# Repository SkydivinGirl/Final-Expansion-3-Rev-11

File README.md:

# Final-Expansion-3-Rev-11
VIC-20 Final Expansion 3 Rev 11 Cartridge

This repository contains everything needed to produce a Final Expansion Rev 11 cartridge for the VIC-20 computer.  It's a bit unorganized but the latest versions of the files should be the ones to use.

This project was created to make assembly easier than earlier versions of the Final Expansion 3 cartridge.

The board layouts were created by Fredric Blåholtz.  The 3D case design were created by Thomas Christoph.  The labels, BOM, and most of the other project files were created by Heather Kent.  Preloaded games were prvided by Jeff Daniels of the VIC-20 Denial forum (sleepingelephant.com/ipw-web/bulletin/bb/index.php).  Firmware and other files were created by others.

The 3D Case design has a different license that allows for printing your own case but you are not allowed to sell them.  Read the license in the zip file for details on the license limitations.

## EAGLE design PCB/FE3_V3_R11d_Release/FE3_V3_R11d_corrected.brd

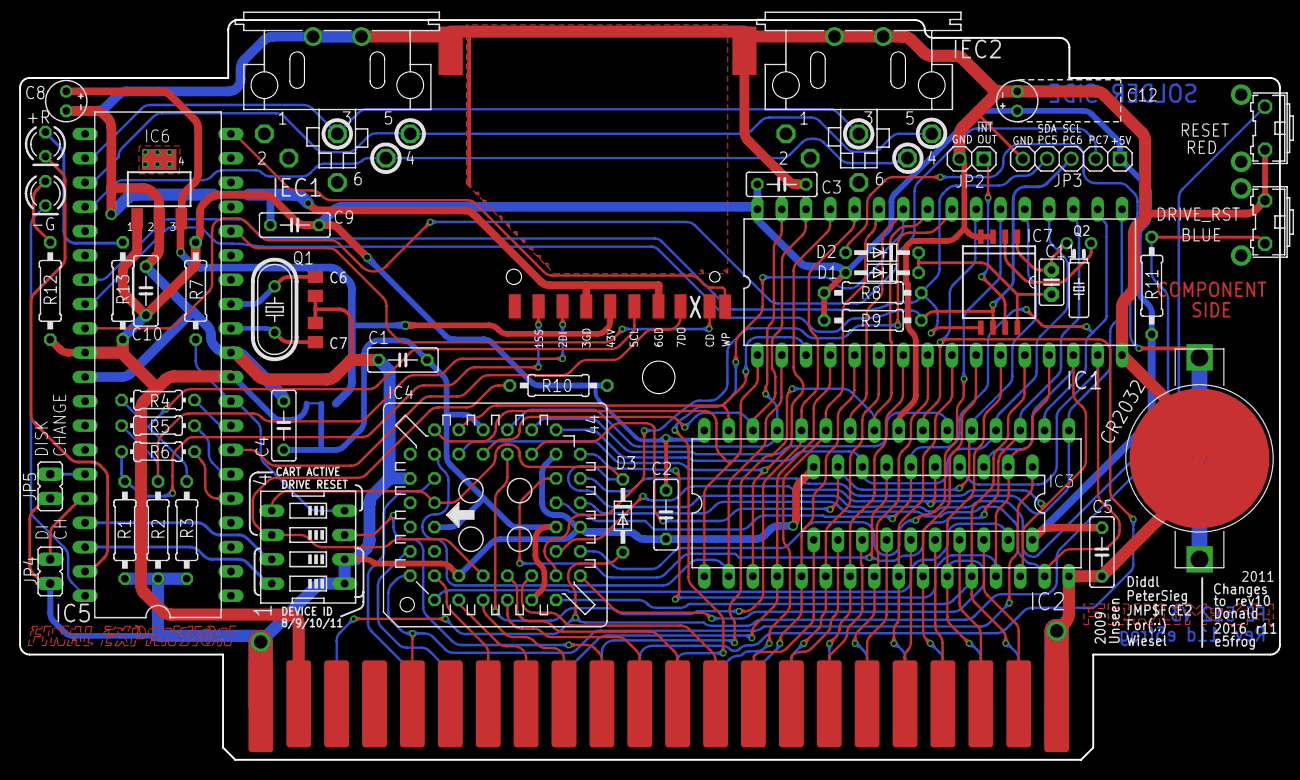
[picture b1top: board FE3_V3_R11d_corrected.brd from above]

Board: 2 copper layers, 131.7 x 77.3 mm, 63 parts (1 on the bottom side), 88 nets.

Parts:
1SS, 2DI, 3GD, 5CL, 6GD, 7DO, 43V: SMD1,27-2,54
+R: LED3MM
-G: LED3MM
C1, C2, C3, C4, C5, C9, C10: 100nF; C050-025X075
C6, C7: 33pF; C0805K
C8: 22µF; E2-4
C11: 22pF; C2.5-2
C12: 100µF; E2-4
CD: SMD1,27-2,54
CR2032: CR2032_RETAINER_PK5
D1, D2, D3: BAT85; DO34-7
DEVICE: EDG-04
DRIVE_RST: B3F-31XX
IC1: AM29F040B; DIL32
IC2: 4Mb-55; DIL32
IC3: 74LS245N; DIL20
IC4: CPLD-ATF1504-AS; S44
IC5: ATMEGA1284P; DIL40
IC6: 3V3REG_1703; SOT223
IC7: PCF8583T; SOT176-1
IEC1, IEC2: MAB6H
JP2: 1X02
JP3: 1X05
JP4, JP5: JP1
NC_9: SMD1,27-2,54
PAD1, PAD2: SMD2,54-5,08
Q1: 8.000MHz; HC49U-V
Q2: 32768Hz; TC26H
R1, R2, R3: 3k3; 0207/10
R4, R5, R6: 1k8; 0204/7
R7, R10, R11: 10k; 0207/10
R8, R9: 1k8; 0207/10
R12, R13: 470; 0207/10
RESET: B3F-31XX
U$2: VIC-20_EXPANSION
V-INT: SJ_2
WP: SMD1,27-2,54

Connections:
3V3: 43V.1, C8.+, IC6.3, V-INT.1
!C_RESET: D3.A, RESET.2, U$2.P$25
!RESET: D3.C, DEVICE.5, DRIVE_RST.1, IC4.1, R11.1
!WE: IC1.31, IC2.29, IC4.33
+5V: C2.1, C3.1, C5.1, C9.1, C10.1, C12.+, D1.A, IC1.32, IC2.32, IC3.20, IC5.10, IC5.30, IC6.1, JP3.1, R7.2, R8.2, R9.2, R10.1, R11.2, R12.1, R13.1, U$2.P$2, V-INT.3
A0: IC1.12, IC2.12, IC4.17, U$2.P$43
A1: IC1.11, IC2.11, IC4.18, U$2.P$42
A2: IC1.10, IC2.10, U$2.P$41
A3: IC1.9, IC2.9, U$2.P$40
A4: IC1.8, IC2.8, U$2.P$39
A5: IC1.7, IC2.7, U$2.P$38
A6: IC1.6, IC2.6, U$2.P$37
A7: IC1.5, IC2.5, U$2.P$36
A8: IC1.27, IC2.27, U$2.P$35
A9: IC1.26, IC2.26, U$2.P$34
A10: IC1.23, IC2.23, U$2.P$33
A11: IC1.25, IC2.25, U$2.P$32
A12: IC1.4, IC2.4, U$2.P$31
A13: IC1.28, IC2.28, IC4.34
A14: IC1.29, IC2.3, IC4.38
A15: IC1.3, IC2.31, IC4.37
A16: IC1.2, IC2.2, IC4.41
A17: IC1.30, IC2.30, IC4.36
A18: IC1.1, IC2.1, IC4.39
BLK1: IC4.16, U$2.P$13
BLK2: IC4.14, U$2.P$12
BLK3: IC4.13, U$2.P$11
BLK5: DEVICE.6, IC4.12, R10.2
CD0: IC3.18, U$2.P$21
CD1: IC3.17, U$2.P$20
CD2: IC3.16, U$2.P$19
CD3: IC3.15, U$2.P$18
CD4: IC3.14, U$2.P$17
CD5: IC3.13, U$2.P$16
CD6: IC3.12, U$2.P$15
CD7: IC3.11, U$2.P$14
C_BLK5: DEVICE.3, U$2.P$10
C_R/W: IC3.1, IC4.6, U$2.P$5
D0: IC1.13, IC2.13, IC3.2, IC4.28
D1: IC1.14, IC2.14, IC3.3, IC4.26
D2: IC1.15, IC2.15, IC3.4, IC4.24
D3: IC1.17, IC2.17, IC3.5, IC4.21
D4: IC1.18, IC2.18, IC3.6, IC4.25
D5: IC1.19, IC2.19, IC3.7, IC4.27
D6: IC1.20, IC2.20, IC3.8, IC4.29
D7: IC1.21, IC2.21, IC3.9, IC4.32
EE/CE: IC1.22, IC4.20
EE/OE: IC1.24, IC4.19
G: IC3.19, IC4.7
GND: 3GD.1, 6GD.1, C1.2, C2.2, C3.2, C4.2, C5.2, C6.2, C7.2, C8.-, C9.2, C10.2, C12.-, CR2032.P$3, DEVICE.1, DEVICE.2, DRIVE_RST.2, IC1.16, IC2.16, IC2.24, IC3.10, IC4.10, IC4.22, IC4.30, IC4.42, IC5.11, IC5.31, IC6.2, IC7.3, IC7.4, IEC1.PE, IEC1.PE@, IEC2.PE, IEC2.PE@, JP2.2, JP3.5, JP4.1, JP5.1, PAD1.1, PAD2.1, R1.1, R2.1, R3.1, RESET.1, U$2.P$1, U$2.P$22, U$2.P$23, U$2.P$44
I2C_N: IC5.27, IC7.5, JP3.4, R8.1
I2C_P: IC5.28, IC7.6, JP3.3, R9.1
IEC_ATN: IC5.22, IEC1.3, IEC2.3
IEC_CLK: IC5.24, IEC1.4, IEC2.4
IEC_DATA: IC5.23, IEC1.5, IEC2.5
IO3: IC4.4, U$2.P$28
LED_GREEN: -G.K, IC5.40
LED_RED: +R.K, IC5.39
unnamed: DEVICE.7, IC5.37
unnamed: IC5.36, JP4.2
unnamed: IC5.35, JP5.2
unnamed: +R.A, R13.2
unnamed: DEVICE.8, IC5.38
unnamed: IC5.29, JP3.2
unnamed: -G.A, R12.2
unnamed: IC5.8, R4.2
unnamed: IC5.6, R5.2
unnamed: IC5.5, R6.2
unnamed: DEVICE.4, IC5.9, R7.1
unnamed: CR2032.P$1, CR2032.P$2, D2.A
unnamed: C7.1, IC5.12, Q1.2
unnamed: C6.1, IC5.13, Q1.1
unnamed: C11.1, D1.C, D2.C, IC7.8
unnamed: C11.2, IC7.1, Q2.2
unnamed: IC7.2, Q2.1
unnamed: IC7.7, JP2.1
RAM1: IC4.11, U$2.P$9
RAM2: IC4.9, U$2.P$8
RAM3: IC4.8, U$2.P$7
RAM/CS: IC2.22, IC4.31
S02: IC4.43, U$2.P$27
SD_CARD_DETECT: CD.1, IC5.16
SD_CARD_SELECT: 1SS.1, R1.2, R6.1
SD_CLOCK: 5CL.1, R3.2, R4.1
SD_DATA_IN: 2DI.1, R2.2, R5.1
SD_DATA_OUT: 7DO.1, IC5.7
SD_WR_PROTECT: IC5.20, WP.1
VCCINT: C1.1, C4.1, IC4.3, IC4.15, IC4.23, IC4.35, V-INT.2

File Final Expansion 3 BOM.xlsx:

Qty | Loc | Markings | Description | Manufacturer # | DigiKey # | Mouser # | Notes
1 | SD | PD00305A | Memory Card Connectors SD CARD RT ANGLE SURF MT PUSH-PUSH | SD-RSMT-2-MQ | 3M5646CT-ND | 517-SD-RSMT-2-MQ
1 | IC6 | MCP1703 | LDO Voltage Regulators Low Iq 250mA LDO Vin 16V maxVout 3.3V | MCP1703-3302E/DB | MCP1703-3302E/DB-ND | 579-MCP1703-3302E/DB
2 | C6,C7 |  | Multilayer Ceramic Capacitors MLCC - SMD/SMT 0603 33pF 50volts C0G 1% | GRM1885C1H330FA01D | 490-9720-1-ND | 81-GRM39C330F50
1 | IC7 | 8583T | Real Time Clock CLK/CALENDAR 240X8 RAM | PCF8583T/5,518 | 568-1085-1-ND | 771-PCF8583TD-T
3 | R1,R2,R3 | O,O R,G | Carbon Film Resistors - Through Hole 3.3K ohm 1/4W 5% | CFR-25JR-52-3K3 | 3.3KQBK-ND | 603-CFR-25JR-523K3
5 | R4,R5,R6,R8,R9 | BR,GRY,R,G | Carbon Film Resistors - Through Hole 1.8K ohm 1/4W 5% | CFR-25JR-52-1K8 | 1.8KQBK-ND | 603-CFR-25JR-521K8
3 | R7,R10,R11 | BR,BL,O,G | Carbon Film Resistors - Through Hole 10K ohm 1/4W 5% | CFR-25JR-52-10K | 10KQBK-ND | 603-CFR-25JR-5210K
2 | R12,R13 | Y,P,BR,G | Carbon Film Resistors - Through Hole 470ohm 1/4W 5% | CFR-25JR-52-470R | 470QBK-ND | 603-CFR-25JR-52470R
3 | D1,D2,D3 |  | Schottky Diodes & Rectifiers SCHOTTKY 30V 200MA | BAT85,113 | 568-1617-1-ND | 771-BAT85-T/R
7 | C1,C2,C3,C4,C5,C9,C10 | 104J | Multilayer Ceramic Capacitors MLCC - Leaded 0.1uF 50volts C0G 5% Radial | FG26C0G1H104JNT06 | 445-173396-1-ND | 810-FG26C0G1H104JNT6
1 | C11 | 220 | Multilayer Ceramic Capacitors MLCC - Leaded 22pF 50volts C0G 5% Radial | FG18C0G1H220JNT06 | 445-173182-1-ND | 810-FG18C0G1H220JNT6
1 | C8 | 22uF10V | Aluminum Electrolytic Capacitors - Leaded 10volts 22uF 4x7 20% 1.5LS | UPW1A220MDD6 | 493-1728-ND | 647-UPW1A220MDD6
1 | C12 | 100uF10V | Aluminum Electrolytic Capacitors - Leaded 100uF 10 Volts 20% | UPW1A101MDD1TD | 493-11391-1-ND | 647-UPW1A101MDD1TD
11 | JP2,JP3,JP4,JP5 |  | 11 Positions Header, Unshrouded Connector 0.100" (2.54mm) Through Hole Gold | 61301411121 | 732-5325-ND | 710-61301411121 | 40-PIN Alternative 61304011121
1 | Q1 | A080F6F | Crystals +/-20ppm 8MHZ FUNDAMENTAL | ABL-8.000MHZ-B2 | 535-9062-ND | 815-ABL-8-B2
1 | Q2 | 32.768000000000001 | Crystals 32.768KHz | AB26T-32.768KHZ | 535-9032-ND | 815-AB26T-32.768KHZ
1 | LED+R |  | Standard LEDs - Through Hole WL-TMRC THT Mono Diffusd Rnd3mm SprRd | 151031SS06000 | 732-5006-ND | 710-151031SS06000 | Alternative? SLX-LX3054ID
1 | LED-G |  | Standard LEDs - Through Hole WL-TMRC THT Mono Diffusd Rnd3mm BrtGn | 151031VS06000 | 732-5008-ND | 710-151031VS06000
2 | IEC |  | Circular DIN Connectors DIN, 6P jack, rt, through hole | SDS-60J | CP-2360-ND | 490-SDS-60J
1 | SW1 | CTS 206-4 | DIP Switches / SIP Switches SPST 4 switch sections | 206-4 | CT2064-ND | 774-2064
1 | B1 |  | Tactile Switches 6x6x5.74mm 160g R/A Red | 1-1825027-2 |  | 506-1-1825027-2
1 | B2 |  | Tactile Switches 6x6x5.74mm 160g R/A Black | 1-1825027-1 | 450-1658-ND | 506-FSMRA4JH04
1 | CR2032 |  | Coin Cell Battery Holders CR2032 BATTERY CLIP | 12BH003-GR |  | 12BH003-GR
1 | IC3 | SN74LS245N | IC BUS TRANSCEIVER 8BIT 20DIP | SN74LS245N | 296-1655-5-ND | 595-SN74LS245N
2 | IC1, IC2 |  | IC & Component Sockets 32P DUAL WIPE DIPSKT | 4832-6000-CP | 3M5470-ND | 517-4832-6000-CP
1 | IC5 |  | IC & Component Sockets 40P DUAL WIPE DIPSKT | 4840-6004-CP | 3M5483-ND | 517-4840-6004-CP
1 | IC4 |  | IC & Component Sockets LCC 44P PBT | PX-44LCC |  | 806-PX-44LCC
1 | IC1 | AM29F040B | AM29F040B-90PI 0928BBA G (512KB Flash) | AM29F040B-90PI | eBay or UTSource
1 | IC2 | AS6C4008 | SRAM 4M, 2.7-5.5V, 55ns 512K x 8 Asynch SRAM | AS6C4008-55PCN | 1450-1027-ND | 913-AS6C4008-55PCN
1 | IC4 | ATF1504AS | CPLD - Complex Programmable Logic Devices CPLD 64 MACROCELL w/ISP STD PWR 5V | ATF1504AS-10JU44 | ATF1504AS-10JU44-ND | 556-AF1504AS10JU44
1 | IC5 | ATMEGA1284 | 8-bit Microcontrollers - MCU AVR 128KB FLSH 4KB EE16KB SRAM-20 MHz | ATMEGA1284-PU | ATMEGA1284-PU-ND | 556-ATMEGA1284-PU

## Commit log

2021-11-18 Initial File Commit
